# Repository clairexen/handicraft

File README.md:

Various unsorted experiments. One branch per year:
- [handicraft-2008](https://github.com/clairexen/handicraft/tree/handicraft-2008)
- [handicraft-2009](https://github.com/clairexen/handicraft/tree/handicraft-2009)
- [handicraft-2010](https://github.com/clairexen/handicraft/tree/handicraft-2010)
- [handicraft-2011](https://github.com/clairexen/handicraft/tree/handicraft-2011)
- [handicraft-2012](https://github.com/clairexen/handicraft/tree/handicraft-2012)
- [handicraft-2013](https://github.com/clairexen/handicraft/tree/handicraft-2013)
- [handicraft-2014](https://github.com/clairexen/handicraft/tree/handicraft-2014)
- [handicraft-2015](https://github.com/clairexen/handicraft/tree/handicraft-2015)
- [handicraft-2016](https://github.com/clairexen/handicraft/tree/handicraft-2016)
- [handicraft-2017](https://github.com/clairexen/handicraft/tree/handicraft-2017)
- [handicraft-2018](https://github.com/clairexen/handicraft/tree/handicraft-2018)
- [handicraft-2019](https://github.com/clairexen/handicraft/tree/handicraft-2019)
- [handicraft-2020](https://github.com/clairexen/handicraft/tree/handicraft-2020)
- [handicraft-2021](https://github.com/clairexen/handicraft/tree/handicraft-2021)
- [handicraft-2022](https://github.com/clairexen/handicraft/tree/handicraft-2022)
- [handicraft-2023](https://github.com/clairexen/handicraft/tree/handicraft-2023)
- [handicraft-2024](https://github.com/clairexen/handicraft/tree/handicraft-2024)

Checking out one year:
```sh
bash -ex clone-year.sh YYYY
```

Checking out all years:
```sh
bash -ex clone-year.sh {2008..2024}
```

Creating a new year:
```sh
create_handicraft_year() { year="$1"; (
	set -ex
	git clone --reference "$PWD" git@github.com:clairexen/handicraft.git handicraft-${year}
	cd handicraft-${year}
	git checkout --orphan handicraft-${year}
	rm *; touch .gitignore; git add -u .gitignore
	git commit -sm "Create handicraft-${year}"
	git push --set-upstream origin handicraft-${year}
	cd ..
	rm -rf handicraft-${year}
	bash -ex clone-year.sh ${year}
); }
create_handicraft_year 2024
```

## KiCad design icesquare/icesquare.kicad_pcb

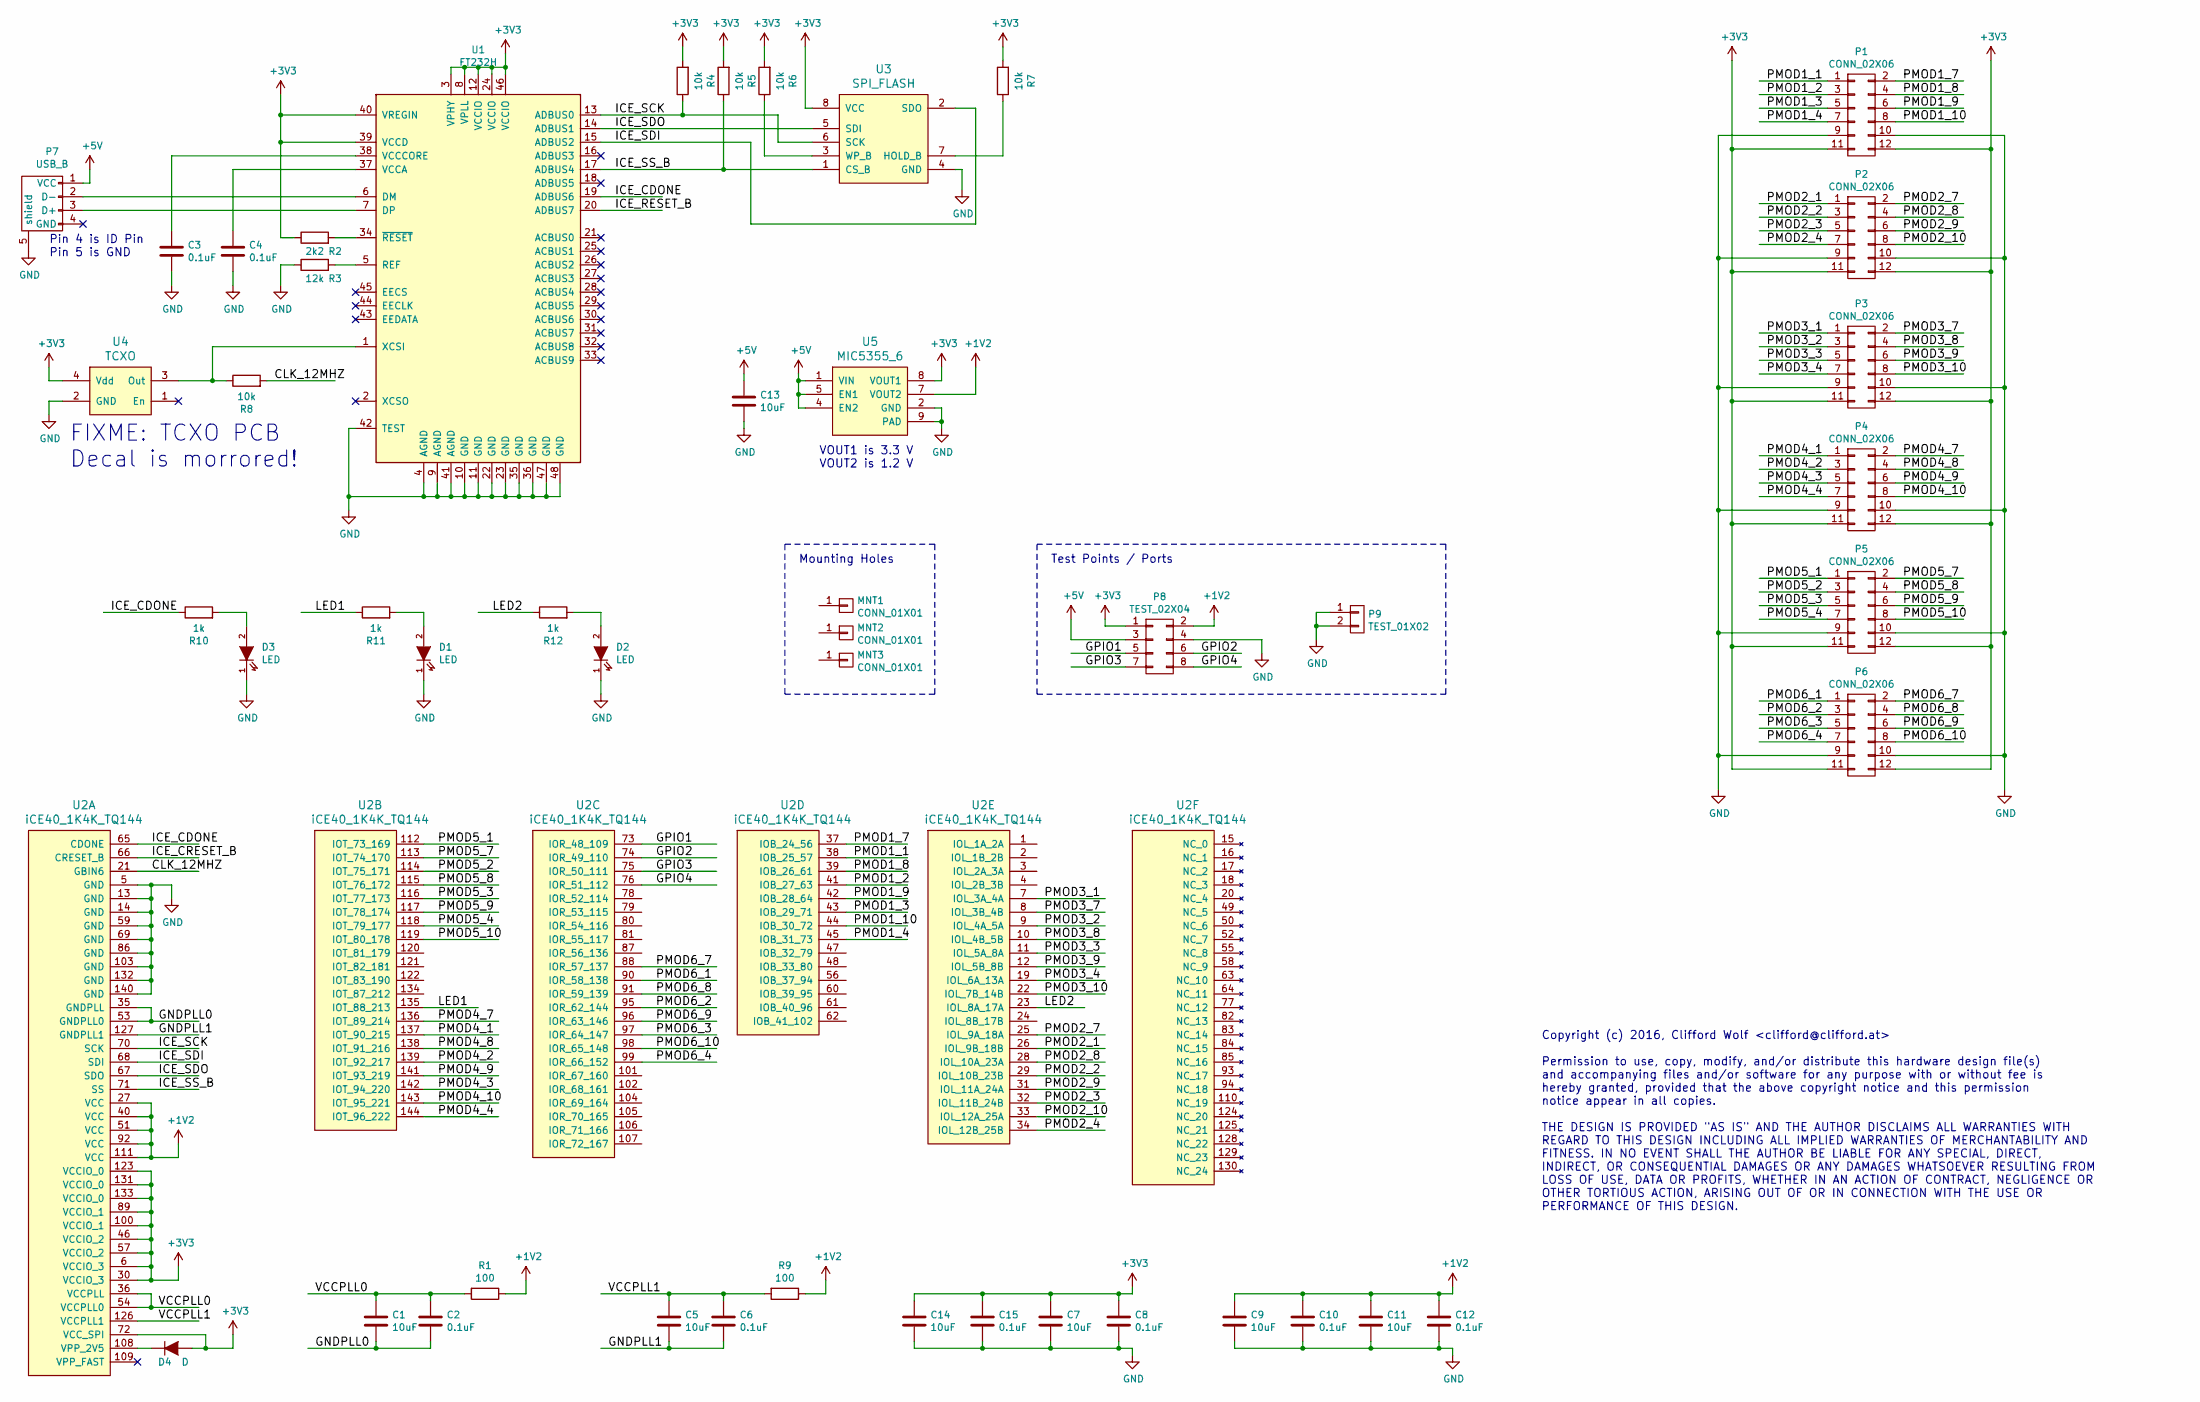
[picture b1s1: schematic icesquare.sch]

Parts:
C1, C5, C7, C9, C11, C13, C14: 10uF; C_0603
C2, C3, C4, C6, C8, C10, C12, C15: 0.1uF; C_0603
D1, D2, D3: LED; LED_0805; DigiKey 511-1292-1-ND
D4: D; SOD-523; DigiKey 641-1332-1-ND
MNT1, MNT2, MNT3: CONN_01X01; MOUNTINGHOLE
P1, P2, P3, P4, P5, P6: CONN_02X06; Socket_Strip_Angled_2x06; DigiKey S5559-ND
P7: USB_B; USB_Micro-B; DigiKey 609-4618-1-ND
P8: TEST_02X04; Pin_Header_Straight_2x04
P9: TEST_01X02; Pin_Header_Straight_1x02
R1, R9: 100; R_0603
R2: 2k2; R_0603
R3: 12k; R_0603
R4, R5, R6, R7, R8: 10k; R_0603
R10, R11, R12: 1k; R_0603
U1: FT232H; LQFP-48_7x7mm_Pitch0.5mm; DigiKey 768-1101-1-ND
U2: iCE40_1K4K_TQ144; LQFP-144_20x20mm_Pitch0.5mm; DigiKey 220-1572-ND
U3: SPI_FLASH; SOIC-8-N; DigiKey 1274-1134-ND
U4: TCXO; DigiKey 535-11724-1-ND
U5: MIC5355_6; MSOP-8-1EP_3x3mm_Pitch0.65mm; DigiKey 576-3880-5-ND

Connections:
+1V2: C9.1, C10.1, C11.1, C12.1, P8.2, R1.1, R9.1, U2.27 (VCC), U2.40 (VCC), U2.51 (VCC), U2.92 (VCC), U2.111 (VCC), U5.7 (VOUT2)
+3V3: C7.1, C8.1, C14.1, C15.1, D4.2 (A), P1.11, P1.12, P2.11, P2.12, P3.11, P3.12, P4.11, P4.12, P5.11, P5.12, P6.11, P6.12, P8.1, R2.1, R4.2, R5.2, R6.2, R7.2, U1.3 (VPHY), U1.8 (VPLL), U1.12 (VCCIO), U1.24 (VCCIO), U1.39 (VCCD), U1.40 (VREGIN), U1.46 (VCCIO), U2.6 (VCCIO_3), U2.30 (VCCIO_3), U2.46 (VCCIO_2), U2.57 (VCCIO_2), U2.72 (VCC_SPI), U2.89 (VCCIO_1), U2.100 (VCCIO_1), U2.123 (VCCIO_0), U2.131 (VCCIO_0), U2.133 (VCCIO_0), U3.8 (VCC), U4.4 (Vdd), U5.8 (VOUT1)
+5V: C13.1, P7.1 (VCC), P8.3, U5.1 (VIN), U5.4 (EN2), U5.5 (EN1)
/CLK_12MHZ: R8.2, U2.21 (GBIN6)
/GNDPLL0: C1.2, C2.2, U2.35 (GNDPLL), U2.53 (GNDPLL0)
/GNDPLL1: C5.2, C6.2, U2.127 (GNDPLL1)
/GPIO1: P8.5, U2.73 (IOR_48_109)
/GPIO2: P8.6, U2.74 (IOR_49_110)
/GPIO3: P8.7, U2.75 (IOR_50_111)
/GPIO4: P8.8, U2.76 (IOR_51_112)
/ICE_CDONE: R10.1, U1.19 (ADBUS6), U2.65 (CDONE)
/ICE_CRESET_B: U2.66 (CRESET_B)
/ICE_RESET_B: U1.20 (ADBUS7)
/ICE_SCK: R4.1, U1.13 (ADBUS0), U2.70 (SCK), U3.6 (SCK)
/ICE_SDI: U1.15 (ADBUS2), U2.68 (SDI), U3.2 (SDO)
/ICE_SDO: U1.14 (ADBUS1), U2.67 (SDO), U3.5 (SDI)
/ICE_SS_B: R5.1, U1.17 (ADBUS4), U2.71 (SS), U3.1 (CS_B)
/LED1: R11.1, U2.135 (IOT_88_213)
/LED2: R12.1, U2.23 (IOL_8A_17A)
/PMOD1_1: P1.1, U2.38 (IOB_25_57)
/PMOD1_2: P1.3, U2.41 (IOB_27_63)
/PMOD1_3: P1.5, U2.43 (IOB_29_71)
/PMOD1_4: P1.7, U2.45 (IOB_31_73)
/PMOD1_7: P1.2, U2.37 (IOB_24_56)
/PMOD1_8: P1.4, U2.39 (IOB_26_61)
/PMOD1_9: P1.6, U2.42 (IOB_28_64)
/PMOD1_10: P1.8, U2.44 (IOB_30_72)
/PMOD2_1: P2.1, U2.26 (IOL_9B_18B)
/PMOD2_2: P2.3, U2.29 (IOL_10B_23B)
/PMOD2_3: P2.5, U2.32 (IOL_11B_24B)
/PMOD2_4: P2.7, U2.34 (IOL_12B_25B)
/PMOD2_7: P2.2, U2.25 (IOL_9A_18A)
/PMOD2_8: P2.4, U2.28 (IOL_10A_23A)
/PMOD2_9: P2.6, U2.31 (IOL_11A_24A)
/PMOD2_10: P2.8, U2.33 (IOL_12A_25A)
/PMOD3_1: P3.1, U2.7 (IOL_3A_4A)
/PMOD3_2: P3.3, U2.9 (IOL_4A_5A)
/PMOD3_3: P3.5, U2.11 (IOL_5A_8A)
/PMOD3_4: P3.7, U2.19 (IOL_6A_13A)
/PMOD3_7: P3.2, U2.8 (IOL_3B_4B)
/PMOD3_8: P3.4, U2.10 (IOL_4B_5B)
/PMOD3_9: P3.6, U2.12 (IOL_5B_8B)
/PMOD3_10: P3.8, U2.22 (IOL_7B_14B)
/PMOD4_1: P4.1, U2.137 (IOT_90_215)
/PMOD4_2: P4.3, U2.139 (IOT_92_217)
/PMOD4_3: P4.5, U2.142 (IOT_94_220)
/PMOD4_4: P4.7, U2.144 (IOT_96_222)
/PMOD4_7: P4.2, U2.136 (IOT_89_214)
/PMOD4_8: P4.4, U2.138 (IOT_91_216)
/PMOD4_9: P4.6, U2.141 (IOT_93_219)
/PMOD4_10: P4.8, U2.143 (IOT_95_221)
/PMOD5_1: P5.1, U2.112 (IOT_73_169)
/PMOD5_2: P5.3, U2.114 (IOT_75_171)
/PMOD5_3: P5.5, U2.116 (IOT_77_173)
/PMOD5_4: P5.7, U2.118 (IOT_79_177)
/PMOD5_7: P5.2, U2.113 (IOT_74_170)
/PMOD5_8: P5.4, U2.115 (IOT_76_172)
/PMOD5_9: P5.6, U2.117 (IOT_78_174)
/PMOD5_10: P5.8, U2.119 (IOT_80_178)
/PMOD6_1: P6.1, U2.90 (IOR_58_138)
/PMOD6_2: P6.3, U2.95 (IOR_62_144)
/PMOD6_3: P6.5, U2.97 (IOR_64_147)
/PMOD6_4: P6.7, U2.99 (IOR_66_152)
/PMOD6_7: P6.2, U2.88 (IOR_57_137)
/PMOD6_8: P6.4, U2.91 (IOR_59_139)
/PMOD6_9: P6.6, U2.96 (IOR_63_146)
/PMOD6_10: P6.8, U2.98 (IOR_65_148)
/VCCPLL0: C1.1, C2.1, R1.2, U2.36 (VCCPLL), U2.54 (VCCPLL0)
/VCCPLL1: C5.1, C6.1, R9.2, U2.126 (VCCPLL1)
GND: C3.2, C4.2, C7.2, C8.2, C9.2, C10.2, C11.2, C12.2, C13.2, C14.2, C15.2, D1.1 (K), D2.1 (K), D3.1 (K), P1.9, P1.10, P2.9, P2.10, P3.9, P3.10, P4.9, P4.10, P5.9, P5.10, P6.9, P6.10, P7.5 (shield), P8.4, P9.1, P9.2, R3.1, U1.4 (AGND), U1.9 (AGND), U1.10 (GND), U1.11 (GND), U1.22 (GND), U1.23 (GND), U1.35 (GND), U1.36 (GND), U1.41 (AGND), U1.42 (TEST), U1.47 (GND), U1.48 (GND), U2.5 (GND), U2.13 (GND), U2.14 (GND), U2.59 (GND), U2.69 (GND), U2.86 (GND), U2.103 (GND), U2.132 (GND), U2.140 (GND), U3.4 (GND), U4.2 (GND), U5.2 (GND), U5.9 (PAD)
unnamed: C3.1, U1.38 (VCCCORE)
unnamed: C4.1, U1.37 (VCCA)
unnamed: D1.2 (A), R11.2
unnamed: D2.2 (A), R12.2
unnamed: D3.2 (A), R10.2
unnamed: D4.1 (K), U2.108 (VPP_2V5)
unnamed: P7.2 (D-), U1.6 (DM)
unnamed: P7.3 (D+), U1.7 (DP)
unnamed: R2.2, U1.34 (~RESET)
unnamed: R3.2, U1.5 (REF)
unnamed: R6.1, U3.3 (WP_B)
unnamed: R7.1, U3.7 (HOLD_B)
unnamed: R8.1, U1.1 (XCSI), U4.3 (Out)

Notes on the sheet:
Test Points / Ports
Mounting Holes
Copyright (c) 2016, Clifford Wolf <clifford@clifford.at> Permission to use, copy, modify, and/or distribute this hardware design file(s) and accompanying files and/or software for any purpose with or without fee is hereby granted, provided that the above copyright notice and this permission notice 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
Pin 4 is ID Pin Pin 5 is GND
VOUT1 is 3.3 V VOUT2 is 1.2 V
FIXME: TCXO PCB Decal is morrored!

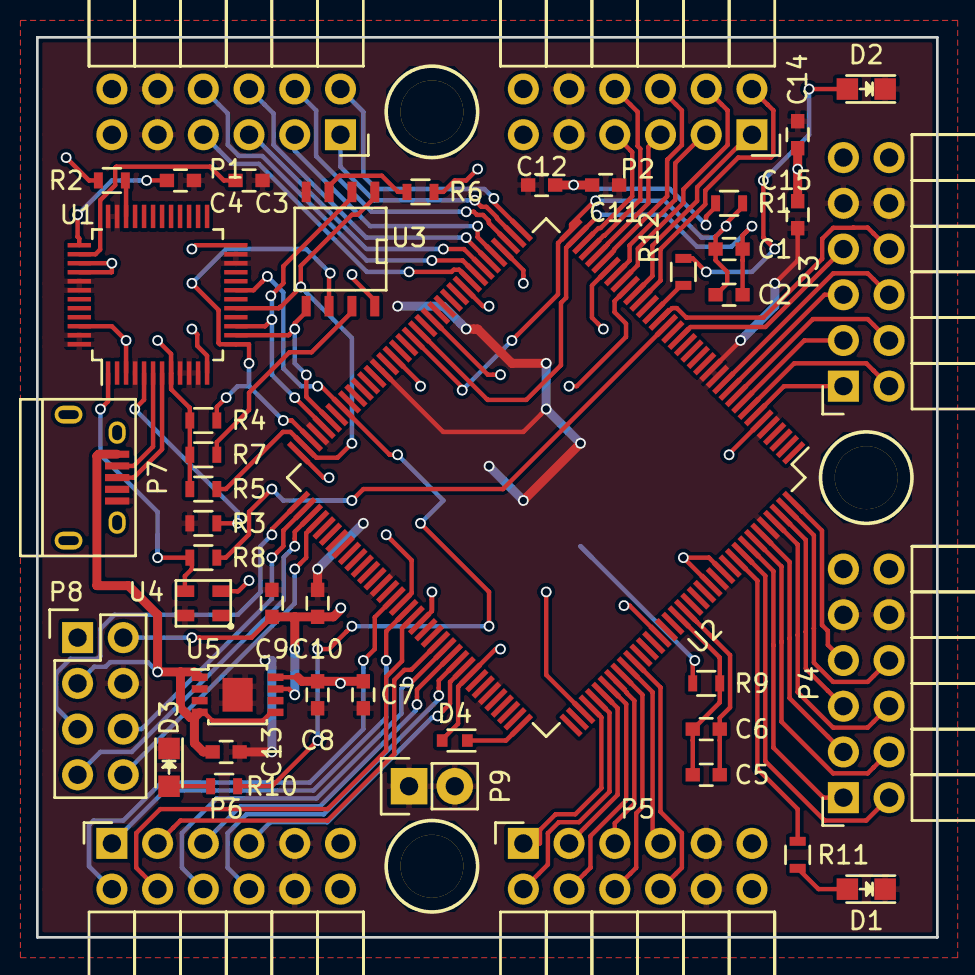
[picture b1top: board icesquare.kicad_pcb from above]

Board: 2 copper layers, 50.0 x 50.0 mm, 48 parts (0 on the bottom side), 81 nets.

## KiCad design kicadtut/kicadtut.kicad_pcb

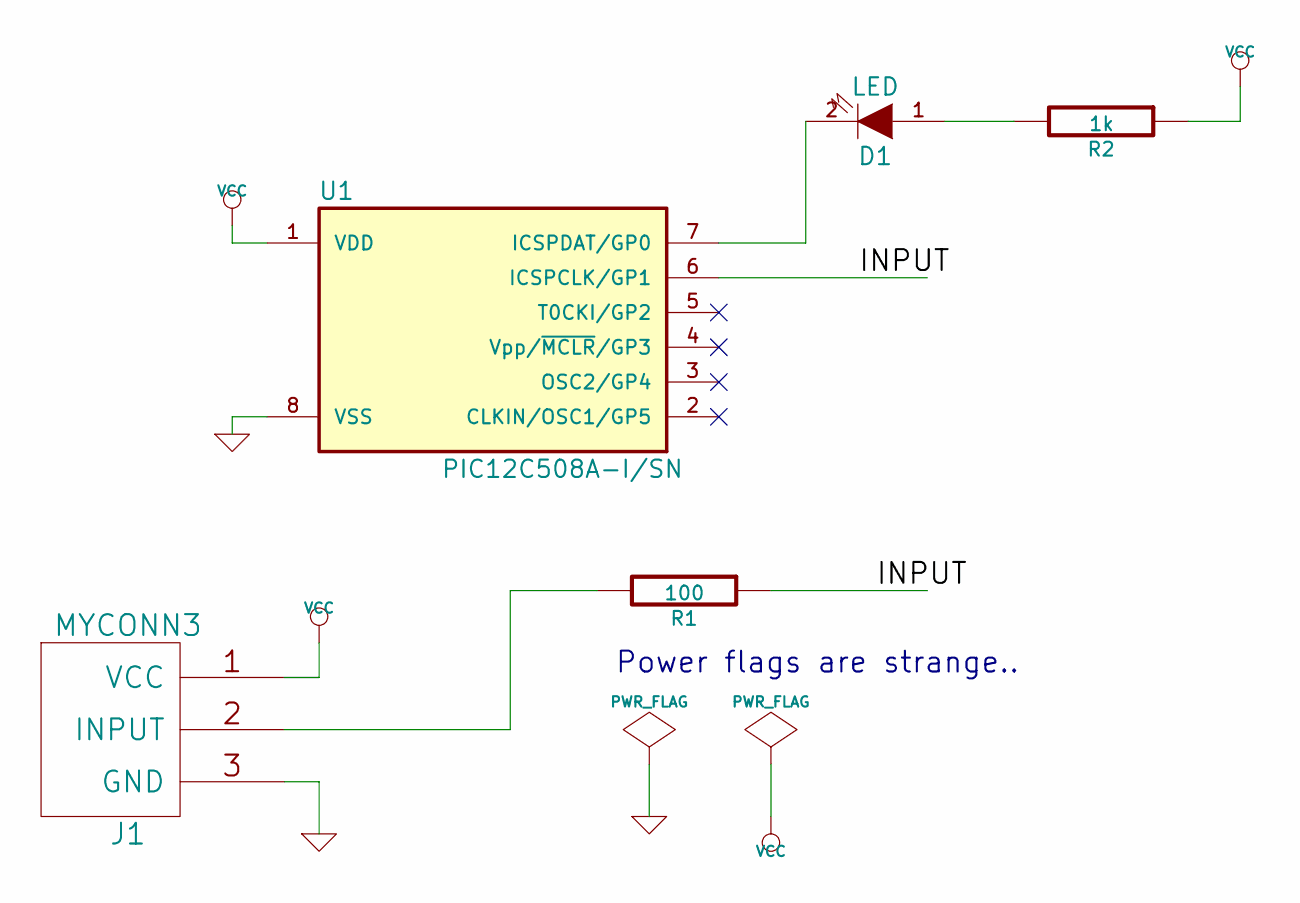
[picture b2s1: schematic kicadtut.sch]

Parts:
D1: LED; LED-5MM
J1: MYCONN3
R1: 100
R2: 1k
U1: PIC12C508A-I/SN

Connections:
/INPUT: R1.1, U1.6 (ICSPCLK/GP1)
GND: J1.3 (GND), U1.8 (VSS)
unnamed: D1.1 (A), R2.2
unnamed: D1.2 (K), U1.7 (ICSPDAT/GP0)
unnamed: J1.2 (INPUT), R1.2
VCC: J1.1 (VCC), R2.1, U1.1 (VDD)

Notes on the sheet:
Power flags are strange..

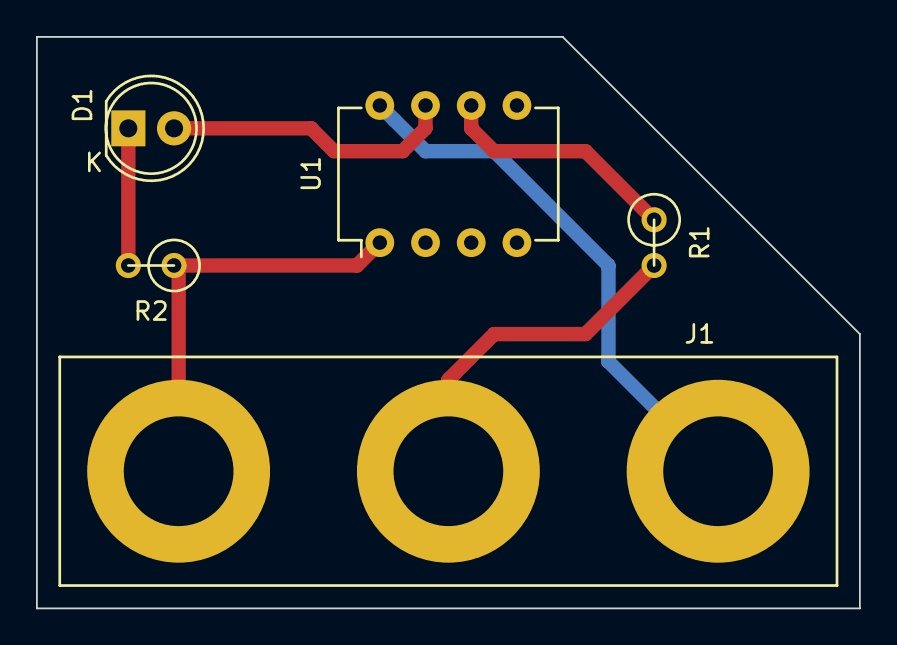
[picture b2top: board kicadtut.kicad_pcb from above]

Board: 2 copper layers, 45.7 x 31.7 mm, 5 parts (0 on the bottom side), 6 nets.

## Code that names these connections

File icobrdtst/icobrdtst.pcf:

set_io CLK12MHZ R9

set_io LED1 C8
set_io LED2 F7
set_io LED3 K9

set_io RASPI_11 A5
set_io RASPI_12 F9
set_io RASPI_15 E9
set_io RASPI_16 E10
set_io RASPI_19 A6
set_io RASPI_21 A7
set_io RASPI_24 H6
set_io RASPI_35 D10
set_io RASPI_36 D9
set_io RASPI_38 C9
set_io RASPI_40 C10

set_io PMOD1_1  A1
set_io PMOD1_2  A2
set_io PMOD1_3  B1
set_io PMOD1_4  B2
set_io PMOD1_7  D8
set_io PMOD1_8  C7
set_io PMOD1_9  C6
set_io PMOD1_10 B3

set_io PMOD2_1  A11
set_io PMOD2_2  B11
set_io PMOD2_3  A16
set_io PMOD2_4  A15
set_io PMOD2_7  A9
set_io PMOD2_8  B9
set_io PMOD2_9  A10
set_io PMOD2_10 B10

set_io PMOD3_1  T3
set_io PMOD3_2  T2
set_io PMOD3_3  T1
set_io PMOD3_4  R2
set_io PMOD3_7  T8
set_io PMOD3_8  T7
set_io PMOD3_9  T6
set_io PMOD3_10 T5

set_io PMOD4_1  T10
set_io PMOD4_2  T9
set_io PMOD4_3  T16
set_io PMOD4_4  T15
set_io PMOD4_7  R14
set_io PMOD4_8  T14
set_io PMOD4_9  T13
set_io PMOD4_10 T11

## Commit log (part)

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2026-02-10 random position offsets
2026-02-10 add --lr-warmup
2026-02-10 fix position_shift
2026-02-10 fix lr header
2026-02-10 fix lr schedule
2026-02-10 add lr decay
2026-02-10 implement [no]-detach-ctx
2026-02-10 layout modifiers
2026-02-10 Add --cycles +N syntax
2026-02-10 add --lr-steady
2026-02-11 proper "test" mode
2026-02-11 add eval subcommand
2026-02-11 add eval --rand N
2026-02-11 switch to 32k vocab
2026-02-11 add "reset" subcommand
2026-02-11 set default to --cycles +1
2026-02-11 add test --attn-map
2026-02-11 add fractions to layout micro-language
2026-02-11 add upper case E D F N to layout mini-language
2026-02-11 more batch layout mini lang tweaks
2026-02-11 add hist.py --filter N
2026-02-11 hist.py --scatter
2026-02-11 add hist.py --median N
2026-02-12 add shuffled wp datasets
2026-02-12 datasets update
2026-02-12 update tokenizer
2026-02-14 update notes
2026-02-14 fix coprus sampling
2026-02-14 add plot.py
2026-02-14 rm hist.py
2026-02-14 rewrite LR schedule
2026-02-14 new defaults
2026-02-17 updaye notes
2026-02-17 add T/R [..]-block modifyers
2026-03-01 Revert first implementation of RoPE
    This reverts commit 7474a531c65da88d489f1502c3c7bad79a3e0046.
2026-03-01 add RoPE
2026-03-01 notes
2026-03-01 add think embeddings
2026-03-01 add think 2x 3x 4x
2026-03-01 more thinking
2026-03-01 cli --n-pos / --block-size
2026-03-01 more block_size -> n_pos renaming
2026-03-01 add --small
2026-03-01 update corpus.py: per file limits
2026-03-01 add corpus.py tokenizer --tokipona
2026-03-01 Add vocab_30000 (new default vocab)
2026-03-01 bugfix
2026-03-01 install tmux on pods
2026-03-01 update pod.sh peek
2026-03-01 add plot expr support
2026-03-01 add plot expr support in --list mode
2026-03-01 add plot expr support for comparators
2026-03-01 add plot --plot-fill-sign
2026-03-01 add H/h flag to layout language
2026-03-02 increas tokipona_english batch size to 200
2026-03-02 rm tokipona_english duplicate articles
2026-03-02 update tokipona_english corpus
2026-03-03 half-width embeddings
2026-03-03 n_embd -> n_width
2026-03-03 remove position embeddings
2026-03-03 Replace > in layout mini lang with #
2026-03-03 think+RoPE bugfix
2026-03-03 think bugfix
2026-03-03 think loop_ln bugfix
2026-03-03 bugfix typo
2026-03-03 add extra metrics
2026-03-03 add --detach-think-span N
2026-03-04 add Ny to batch layout syntax
2026-03-04 fix "noattn" handling, add uppercase X layout syntax
2026-03-04 add rpwd.py
2026-03-04 new kv_cache_list_balance
2026-03-05 Update README to include links for notes and implementation
2026-03-05 add --generate-with-decode
2026-03-05 add b/B modifiers
2026-03-05 12x more RoPE
2026-03-05 add `h` (halt) modifier
2026-03-09 add carpe proposal
2026-03-09 rope on full width by default
2026-03-10 udate
2026-03-10 add --align-articles
2026-03-10 eval update
2026-03-10 add n_query
2026-03-10 rename CARPE -> CARPET
2026-03-10 hotfix
2026-03-11 fix n_query implementation
2026-03-11 improve runtime
2026-03-11 improve performance
2026-03-13 carpetvsrope
2026-03-13 final CARPET versions and tests
2026-03-13 Add RoPE-XL
2026-03-13 add minimal SANE
2026-03-13 SANE-ify "reverse" mode
2026-03-13 add `P` drop-out encoder
2026-03-14 add `S` modifier
2026-03-14 add --use-rope-vr
2026-03-14 add --use-rope-vr-all
2026-03-14 add ropexlvreval data and plot
2026-03-14 add ropexlvrplot pngs
2026-03-14 ropexlvr update
2026-03-14 remove --use-carpet --use-carpet2 --use-carpet3
2026-03-14 Add gsm8k corpus
2026-03-17 SANE implementation
2026-03-21 Revert "update"
    This reverts commit 68159ee8e3a5f7c48c2a6ee7561b4533331a1881.
2026-03-26 add vocab_60000
2026-03-28 add yrefresh in addition to xrefresh
2026-03-28 add --use-yscale
